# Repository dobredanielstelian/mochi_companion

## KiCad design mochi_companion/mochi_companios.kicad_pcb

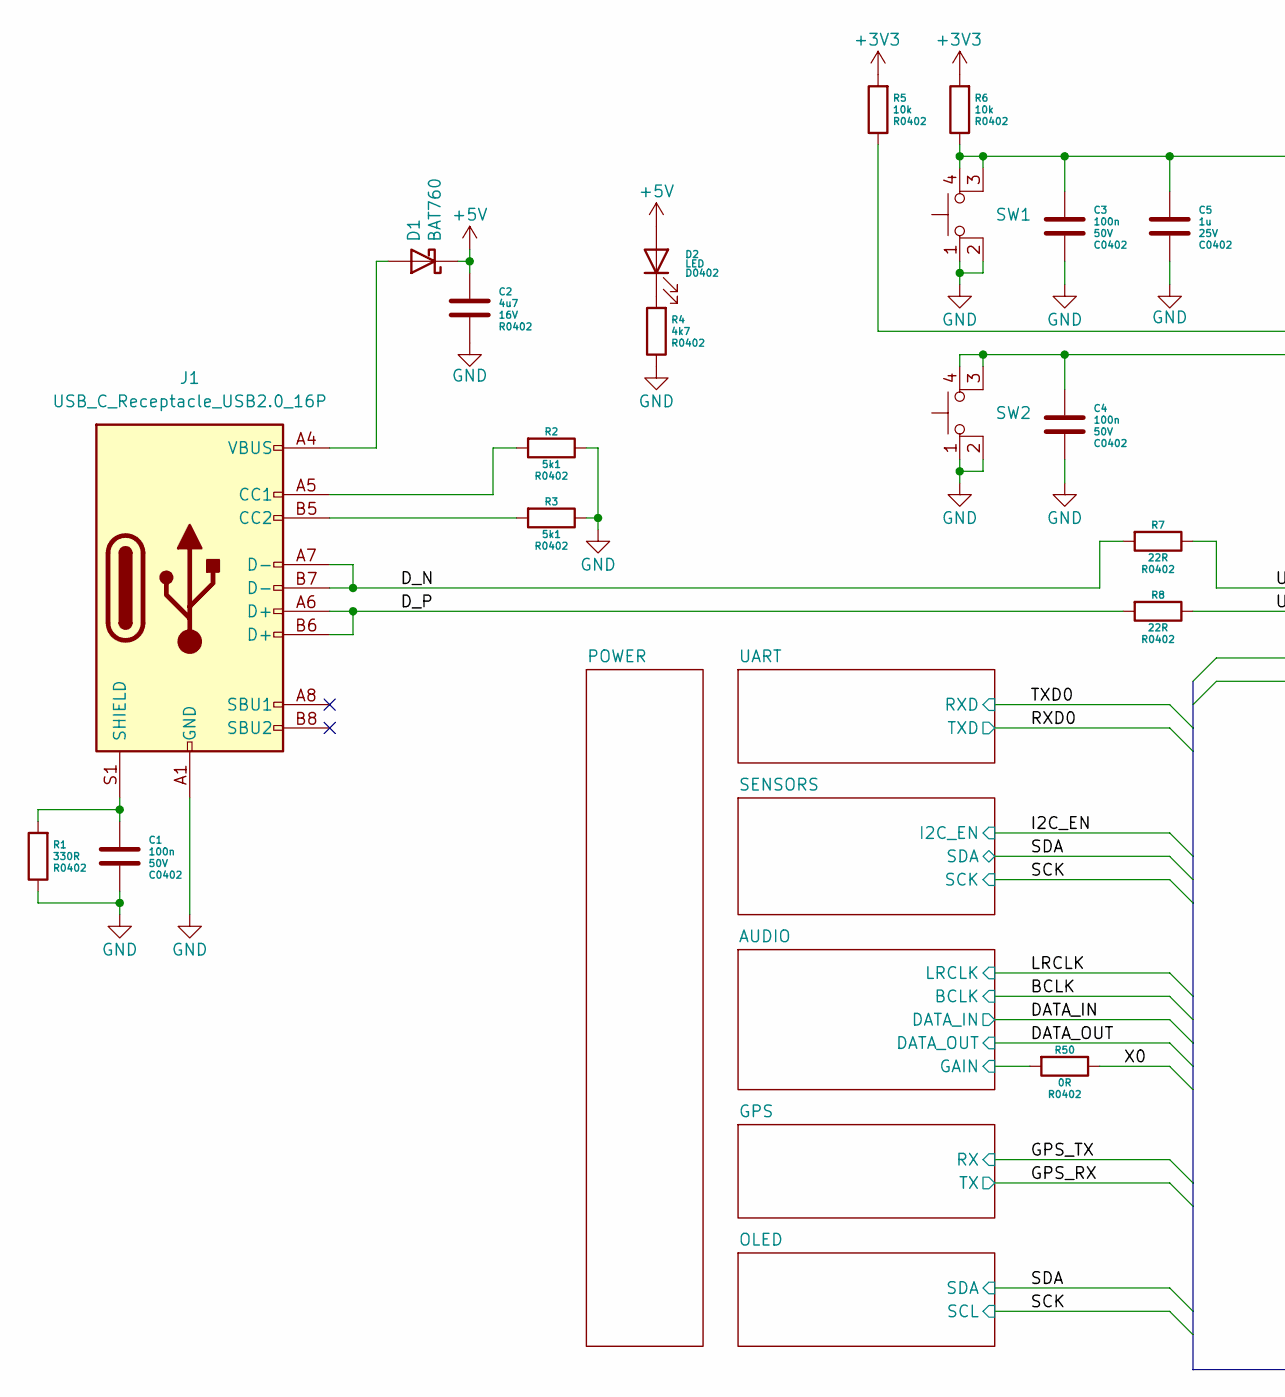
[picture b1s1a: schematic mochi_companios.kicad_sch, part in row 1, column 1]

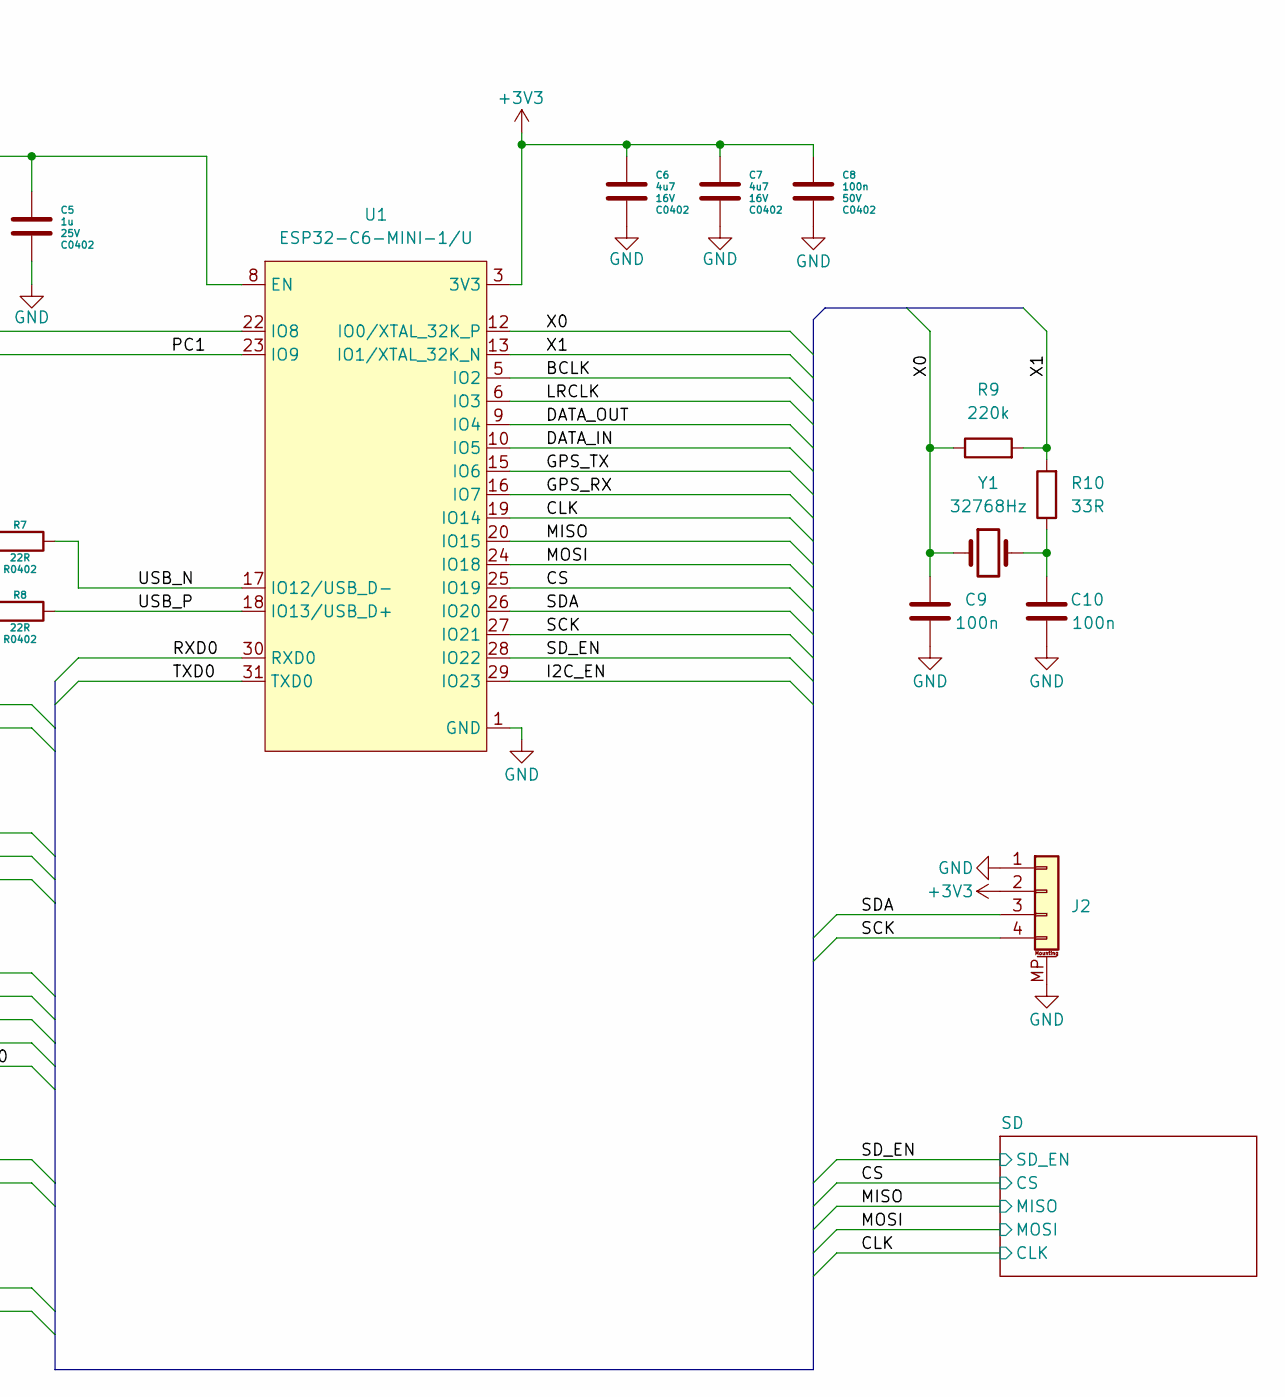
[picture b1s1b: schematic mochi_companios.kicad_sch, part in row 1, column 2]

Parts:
C1, C3, C4, C8, C9, C10: 100n; C_0402_1005Metric
C2, C6, C7: 4u7; C_0402_1005Metric
C5: 1u; C_0402_1005Metric
D1: BAT760; D_SOD-323
D2: LED; D_0402_1005Metric
J1: USB_C_Receptacle_USB2.0_16P; USB_C_Receptacle_Palconn_UTC16-G
J2: Conn_01x04_MountingPin; JST_SH_SM04B-SRSS-TB_1x04-1MP_P1.00mm_Horizontal
R1: 330R; R_0402_1005Metric
R2, R3: 5k1; R_0402_1005Metric
R4: 4k7; R_0402_1005Metric
R5, R6: 10k; R_0402_1005Metric
R7, R8: 22R; R_0402_1005Metric
R9: 220k; R_0402_1005Metric
R10: 33R; R_0402_1005Metric
R50: 0R; R_0402_1005Metric
SW1, SW2: 1TS026A-2300-0553-CT
U1: ESP32-C6-MINI-1/U; ESP32-C6-MINI-1
Y1: 32768Hz; Crystal_SMD_2012-2Pin_2.0x1.2mm

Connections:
+3V3: C6.1, C7.1, C8.1, J2.2, R5.2, R6.2, U1.3 (3V3); also elsewhere on the board
+5V: C2.1, D1.1 (K), D2.2 (A); also elsewhere on the board
/AUDIO/GAIN: R50.2; also elsewhere on the board
/BCLK: U1.5 (IO2); also elsewhere on the board
/CLK: U1.19 (IO14); also elsewhere on the board
/CS: U1.25 (IO19); also elsewhere on the board
/DATA_IN: U1.10 (IO5); also elsewhere on the board
/DATA_OUT: U1.9 (IO4); also elsewhere on the board
/D_N: J1.A7 (D-), J1.B7 (D-), R7.2
/D_P: J1.A6 (D+), J1.B6 (D+), R8.2
/GPS_RX: U1.16 (IO7); also elsewhere on the board
/GPS_TX: U1.15 (IO6); also elsewhere on the board
/I2C_EN: U1.29 (IO23); also elsewhere on the board
/LRCLK: U1.6 (IO3); also elsewhere on the board
/MISO: U1.20 (IO15); also elsewhere on the board
/MOSI: U1.24 (IO18); also elsewhere on the board
/PC1: C4.1, SW2.3 (K), SW2.4 (A), U1.23 (IO9)
/RXD0: U1.30 (RXD0); also elsewhere on the board
/SCK: J2.4, U1.27 (IO21); also elsewhere on the board
/SDA: J2.3, U1.26 (IO20); also elsewhere on the board
/SD_EN: U1.28 (IO22); also elsewhere on the board
/TXD0: U1.31 (TXD0); also elsewhere on the board
/USB_N: R7.1, U1.17 (IO12/USB_D-)
/USB_P: R8.1, U1.18 (IO13/USB_D+)
/X0: C9.1, R9.1, R50.1, U1.12 (IO0/XTAL_32K_P), Y1.1
/X1: R9.2, R10.2, U1.13 (IO1/XTAL_32K_N)
GND: C1.2, C2.2, C3.2, C4.2, C5.2, C6.2, C7.2, C8.2, C9.2, C10.2, J1.A1 (GND), J1.A12 (GND), J1.B1 (GND), J1.B12 (GND), J2.1, J2.MP (MountPin), R1.1, R2.1, R3.1, R4.1, SW1.1, SW1.2, SW2.1, SW2.2, U1.1 (GND), U1.2 (GND), U1.11 (GND), U1.14 (GND), U1.36 (GND), U1.37 (GND), U1.38 (GND), U1.39 (GND), U1.40 (GND), U1.41 (GND), U1.42 (GND), U1.43 (GND), U1.44 (GND), U1.45 (GND), U1.46 (GND), U1.47 (GND), U1.48 (GND), U1.49 (GND), U1.50 (GND), U1.51 (GND), U1.52 (GND), U1.53 (GND); also elsewhere on the board
unnamed: C10.1, R10.1, Y1.2
unnamed: D1.2 (A), J1.A4 (VBUS), J1.A9 (VBUS), J1.B4 (VBUS), J1.B9 (VBUS)
unnamed: D2.1 (K), R4.2
unnamed: J1.A5 (CC1), R2.2
unnamed: J1.B5 (CC2), R3.2
unnamed: C1.1, J1.S1 (SHIELD), R1.2
unnamed: C3.1, C5.1, R6.1, SW1.3 (K), SW1.4 (A), U1.8 (EN)
unnamed: R5.1, U1.22 (IO8)
unnamed: U1.4 (NC), U1.7 (NC), U1.21 (NC), U1.32 (NC), U1.33 (NC), U1.34 (NC), U1.35 (NC)

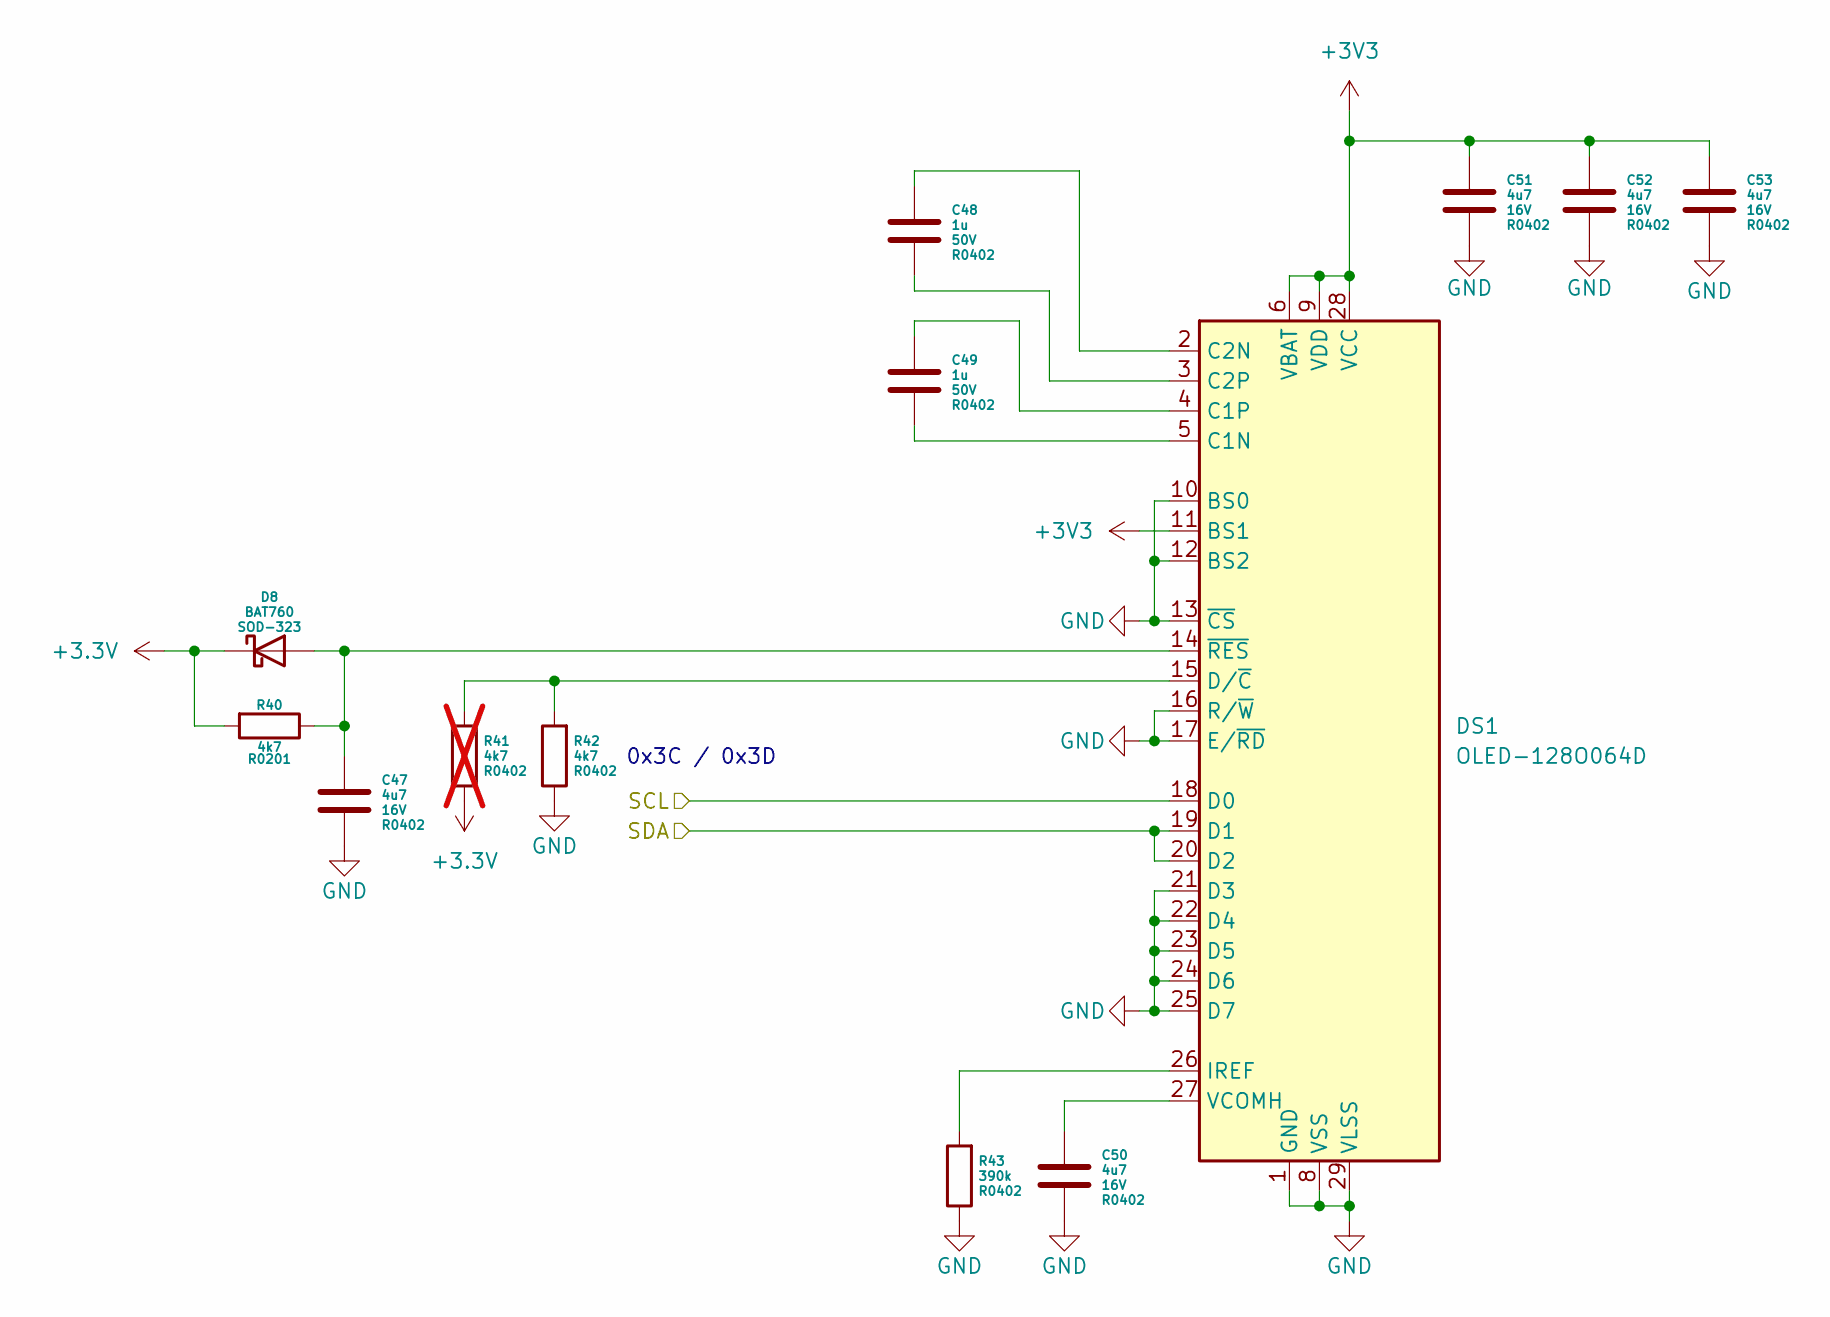
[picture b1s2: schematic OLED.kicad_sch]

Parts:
C47, C50, C51, C52, C53: 4u7; C_0402_1005Metric
C48, C49: 1u; C_0402_1005Metric
D8: BAT760; D_SOD-323
DS1: OLED-128O064D
R40: 4k7; R_0201_0603Metric
R41: 4k7; R_0402_1005Metric; not fitted
R42: 4k7; R_0402_1005Metric
R43: 390k; R_0402_1005Metric

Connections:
+3.3V: D8.1 (K), R40.2, R41.1; also elsewhere on the board
+3V3: C51.1, C52.1, C53.1, DS1.6 (VBAT), DS1.9 (VDD), DS1.11 (BS1), DS1.28 (VCC); also elsewhere on the board
/SCK: DS1.18 (D0); also elsewhere on the board
/SDA: DS1.19 (D1), DS1.20 (D2); also elsewhere on the board
GND: C47.2, C50.2, C51.2, C52.2, C53.2, DS1.1 (GND), DS1.8 (VSS), DS1.10 (BS0), DS1.12 (BS2), DS1.13 (~CS), DS1.16 (R/~W), DS1.17 (E/~RD), DS1.21 (D3), DS1.22 (D4), DS1.23 (D5), DS1.24 (D6), DS1.25 (D7), DS1.29 (VLSS), DS1.30 (GND), R42.1, R43.1; also elsewhere on the board
unnamed: C47.1, D8.2 (A), DS1.14 (~RES), R40.1
unnamed: C49.2, DS1.5 (C1N)
unnamed: C49.1, DS1.4 (C1P)
unnamed: C48.1, DS1.2 (C2N)
unnamed: C48.2, DS1.3 (C2P)
unnamed: DS1.15 (D/~C), R41.2, R42.2
unnamed: DS1.26 (IREF), R43.2
unnamed: C50.1, DS1.27 (VCOMH)

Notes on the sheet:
0x3C / 0x3D

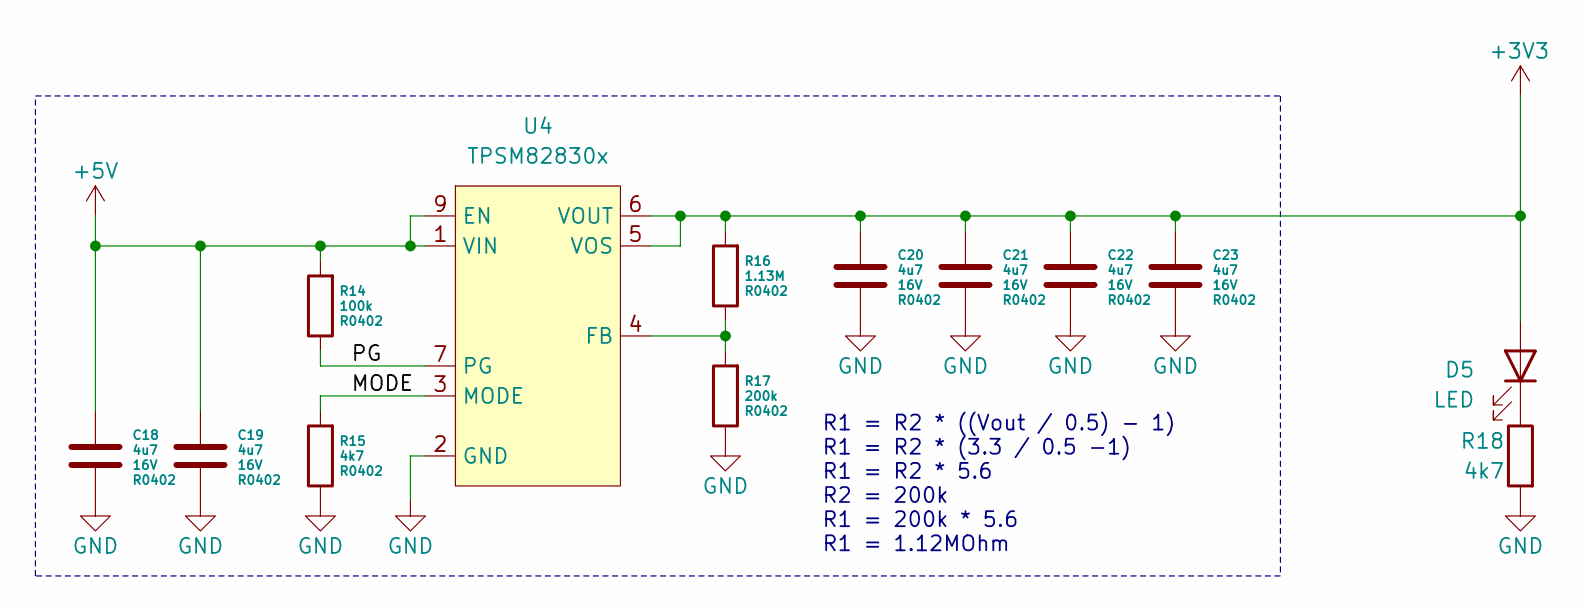
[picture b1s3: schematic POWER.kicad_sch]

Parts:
C18, C19, C20, C21, C22, C23: 4u7; C_0402_1005Metric
D5: LED; D_0402_1005Metric
R14: 100k; R_0402_1005Metric
R15, R18: 4k7; R_0402_1005Metric
R16: 1.13M; R_0402_1005Metric
R17: 200k; R_0402_1005Metric
U4: TPSM82830x; TPSM82830x_QFN-FCMOD

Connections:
+3V3: C20.1, C21.1, C22.1, C23.1, D5.2 (A), R16.2, U4.5 (VOS), U4.6 (VOUT); also elsewhere on the board
+5V: C18.1, C19.1, R14.2, U4.1 (VIN), U4.9 (EN); also elsewhere on the board
/POWER/MODE: R15.2, U4.3 (MODE)
/POWER/PG: R14.1, U4.7 (PG)
GND: C18.2, C19.2, C20.2, C21.2, C22.2, C23.2, R15.1, R17.1, R18.2, U4.2 (GND); also elsewhere on the board
unnamed: D5.1 (K), R18.1
unnamed: R16.1, R17.2, U4.4 (FB)

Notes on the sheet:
R1 = R2 * ((Vout / 0.5) - 1) R1 = R2 * (3.3 / 0.5 -1) R1 = R2 * 5.6 R2 = 200k R1 = 200k * 5.6 R1 = 1.12MOhm

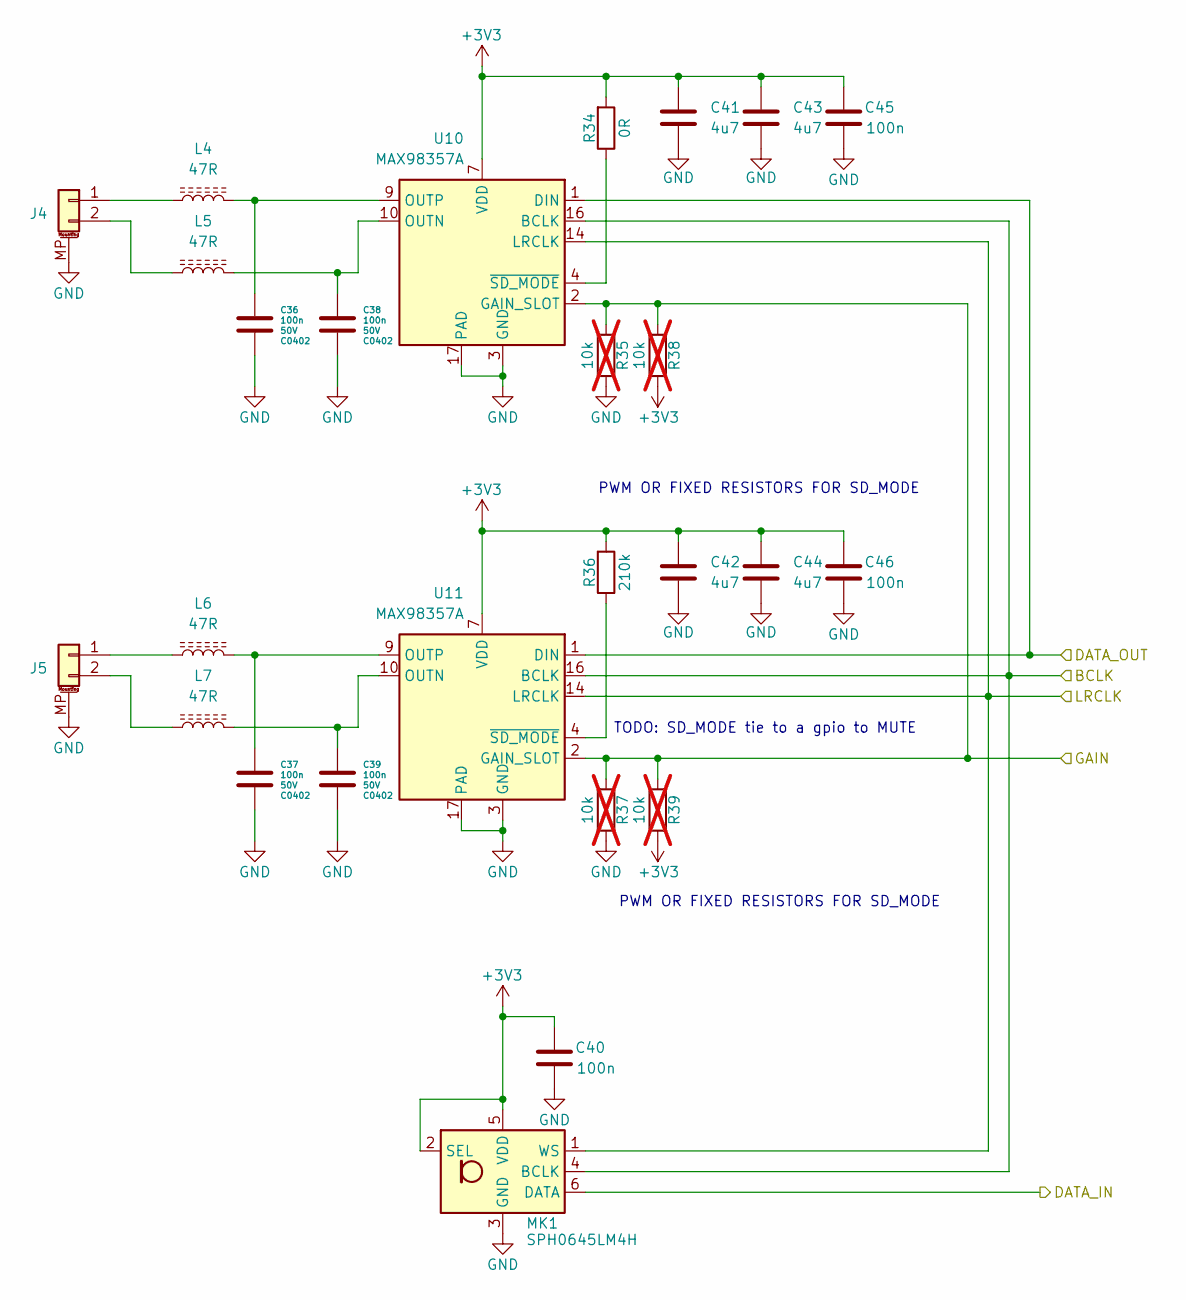
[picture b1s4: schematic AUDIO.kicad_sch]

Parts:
C36, C37, C38, C39, C40, C45, C46: 100n; C_0402_1005Metric
C41, C42, C43, C44: 4u7; C_0402_1005Metric
J4, J5: Conn_01x02_MountingPin; JST_SHL_SM02B-SHLS-TF_1x02-1MP_P1.00mm_Horizontal
L4, L5, L6, L7: 47R; L_0402_1005Metric
MK1: SPH0645LM4H; Knowles_SPH0645LM4H-6_3.5x2.65mm
R34: 0R; R_0402_1005Metric
R35, R37, R38, R39: 10k; R_0402_1005Metric; not fitted
R36: 210k; R_0402_1005Metric
U10, U11: MAX98357A; TQFN-16-1EP_3x3mm_P0.5mm_EP1.23x1.23mm

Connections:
+3V3: C40.1, C41.1, C42.1, C43.1, C44.1, C45.1, C46.1, MK1.2 (SEL), MK1.5 (VDD), R34.2, R36.2, R38.2, R39.2, U10.7 (VDD), U10.8 (VDD), U11.7 (VDD), U11.8 (VDD); also elsewhere on the board
/AUDIO/GAIN: R35.1, R37.1, R38.1, R39.1, U10.2 (GAIN_SLOT), U11.2 (GAIN_SLOT); also elsewhere on the board
/BCLK: MK1.4 (BCLK), U10.16 (BCLK), U11.16 (BCLK); also elsewhere on the board
/DATA_IN: MK1.6 (DATA); also elsewhere on the board
/DATA_OUT: U10.1 (DIN), U11.1 (DIN); also elsewhere on the board
/LRCLK: MK1.1 (WS), U10.14 (LRCLK), U11.14 (LRCLK); also elsewhere on the board
GND: C36.2, C37.2, C38.2, C39.2, C40.2, C41.2, C42.2, C43.2, C44.2, C45.2, C46.2, J4.MP (MountPin), J5.MP (MountPin), MK1.3 (GND), R35.2, R37.2, U10.3 (GND), U10.11 (GND), U10.15 (GND), U10.17 (PAD), U11.3 (GND), U11.11 (GND), U11.15 (GND), U11.17 (PAD); also elsewhere on the board
unnamed: J4.1, L4.1
unnamed: J4.2, L5.1
unnamed: J5.1, L6.1
unnamed: J5.2, L7.1
unnamed: C38.1, L5.2, U10.10 (OUTN)
unnamed: C36.1, L4.2, U10.9 (OUTP)
unnamed: R34.1, U10.4 (~SD_MODE)
unnamed: C39.1, L7.2, U11.10 (OUTN)
unnamed: C37.1, L6.2, U11.9 (OUTP)
unnamed: R36.1, U11.4 (~SD_MODE)

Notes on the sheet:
PWM OR FIXED RESISTORS FOR SD_MODE
TODO: SD_MODE tie to a gpio to MUTE

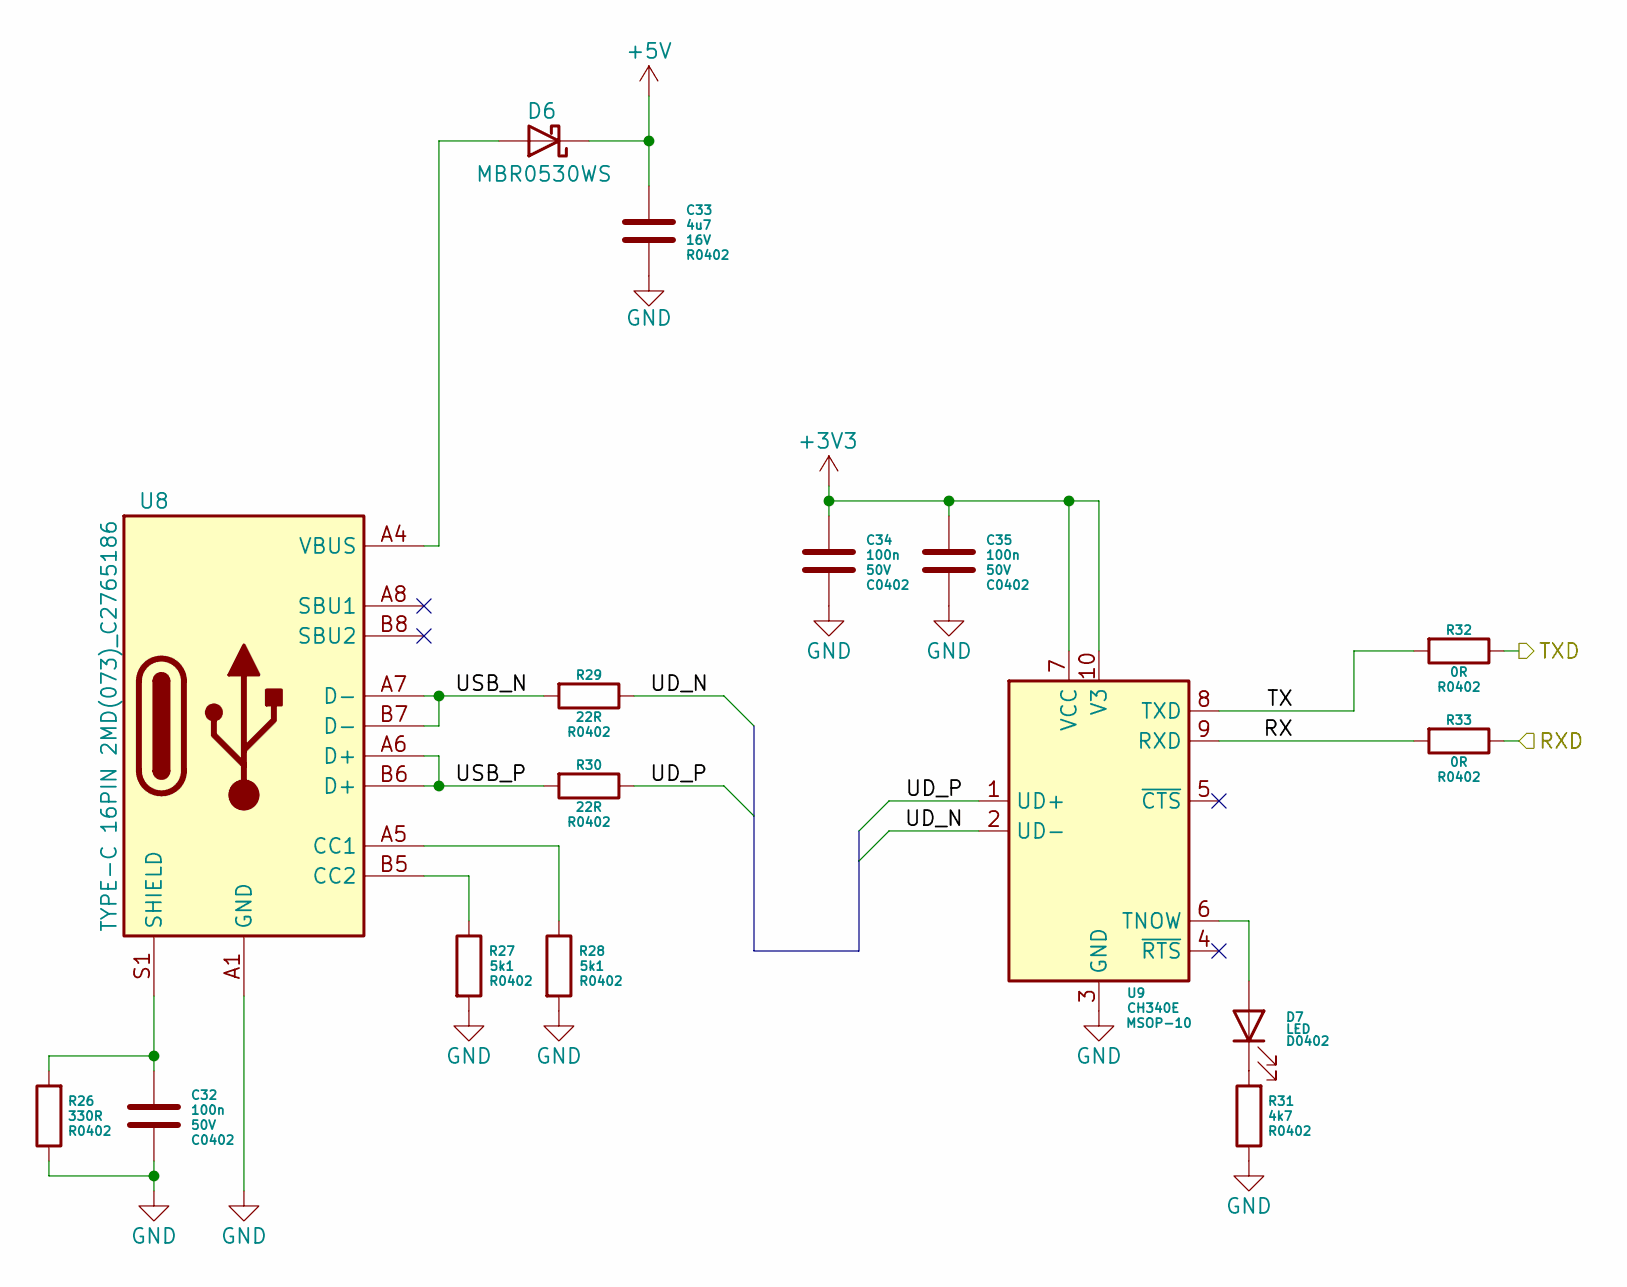
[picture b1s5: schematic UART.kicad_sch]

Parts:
C32, C34, C35: 100n; C_0402_1005Metric
C33: 4u7; C_0402_1005Metric
D6: MBR0530WS; D_SOD-323
D7: LED; D_0402_1005Metric
R26: 330R; R_0402_1005Metric
R27, R28: 5k1; R_0402_1005Metric
R29, R30: 22R; R_0402_1005Metric
R31: 4k7; R_0402_1005Metric
R32, R33: 0R; R_0402_1005Metric
U8: TYPE-C 16PIN 2MD(073)_C2765186; USB_C_Receptacle_Palconn_UTC16-G
U9: CH340E; MSOP-10_3x3mm_P0.5mm

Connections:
+3V3: C34.1, C35.1, U9.7 (VCC), U9.10 (V3); also elsewhere on the board
+5V: C33.1, D6.1 (K); also elsewhere on the board
/RXD0: R32.1; also elsewhere on the board
/TXD0: R33.1; also elsewhere on the board
/UART/RX: R33.2, U9.9 (RXD)
/UART/TX: R32.2, U9.8 (TXD)
/UART/UD_N: R29.1, U9.2 (UD-)
/UART/UD_P: R30.1, U9.1 (UD+)
/UART/USB_N: R29.2, U8.A7 (D-), U8.B7 (D-)
/UART/USB_P: R30.2, U8.A6 (D+), U8.B6 (D+)
GND: C32.2, C33.2, C34.2, C35.2, R26.1, R27.2, R28.2, R31.1, U8.A1 (GND), U8.A12 (GND), U8.B1 (GND), U8.B12 (GND), U9.3 (GND); also elsewhere on the board
unnamed: D6.2 (A), U8.A4 (VBUS), U8.A9 (VBUS), U8.B4 (VBUS), U8.B9 (VBUS)
unnamed: D7.2 (A), U9.6 (TNOW)
unnamed: D7.1 (K), R31.2
unnamed: R28.1, U8.A5 (CC1)
unnamed: R27.1, U8.B5 (CC2)
unnamed: C32.1, R26.2, U8.S1 (SHIELD)

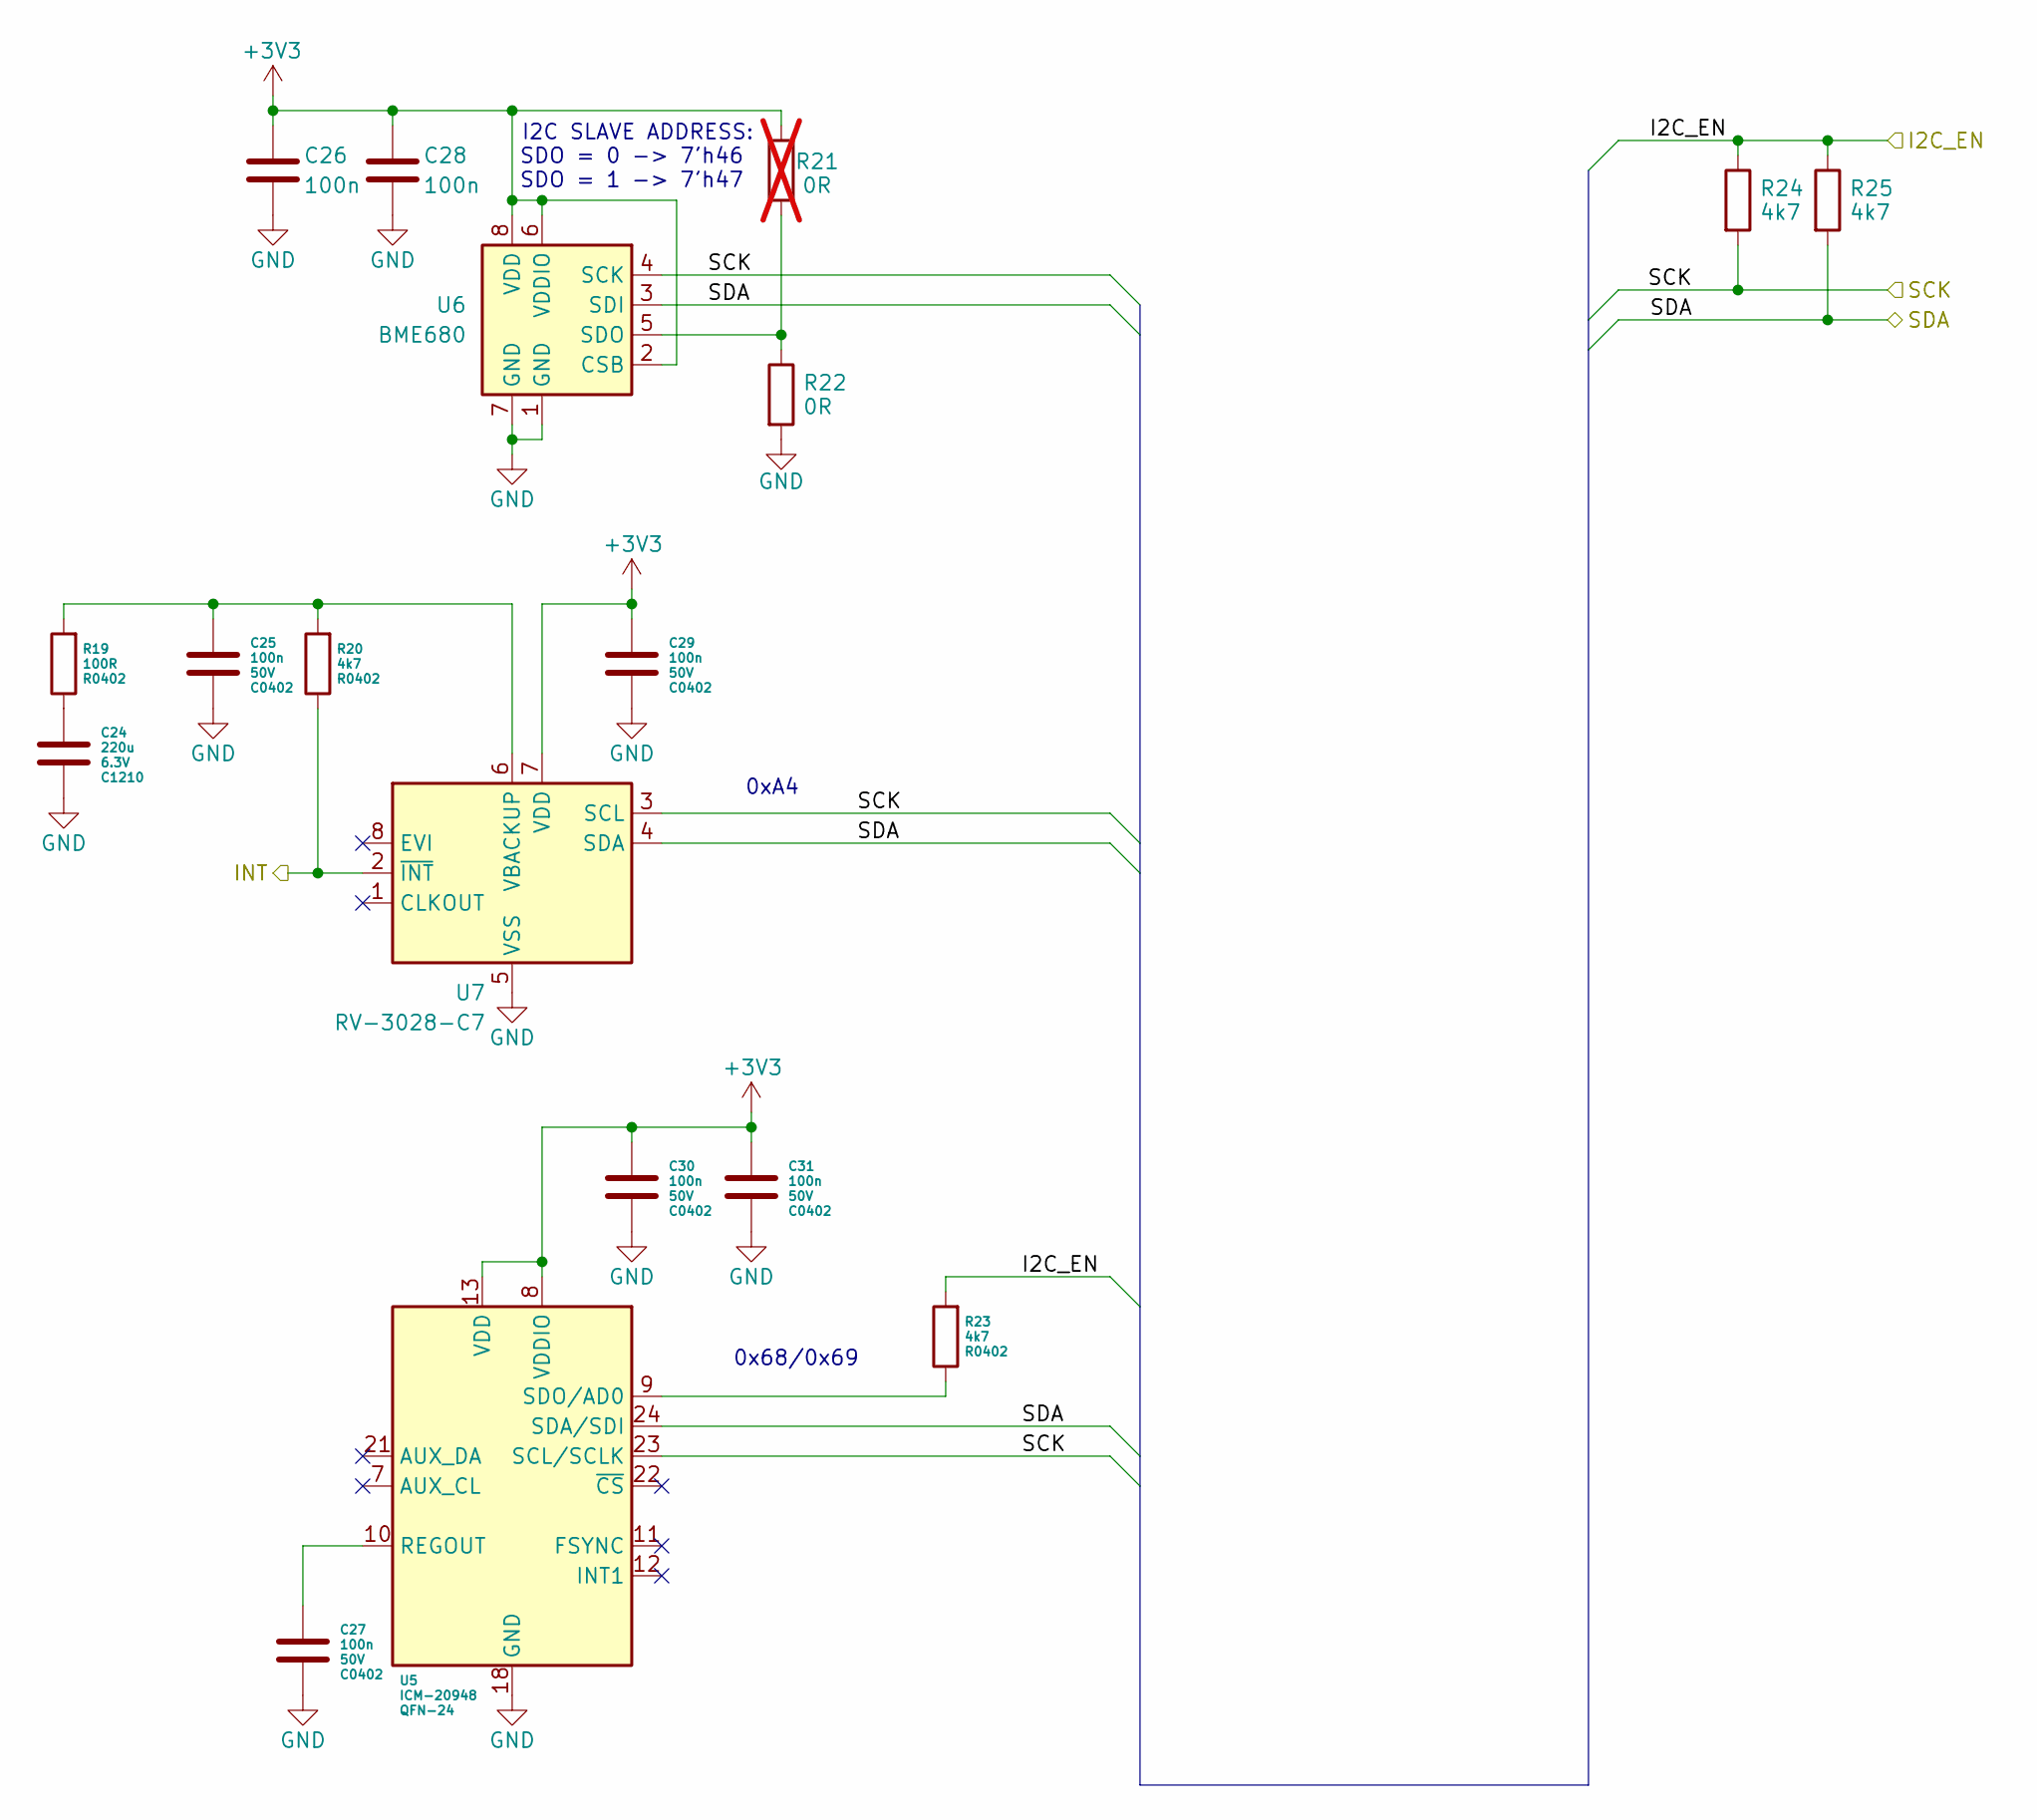
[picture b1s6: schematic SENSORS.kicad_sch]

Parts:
C24: 220u; C_1210_3225Metric
C25, C26, C27, C28, C29, C30, C31: 100n; C_0402_1005Metric
R19: 100R; R_0402_1005Metric
R20, R23, R24, R25: 4k7; R_0402_1005Metric
R21: 0R; R_0402_1005Metric; not fitted
R22: 0R; R_0402_1005Metric
U5: ICM-20948; InvenSense_QFN-24_3x3mm_P0.4mm
U6: BME680; Bosch_LGA-8_3x3mm_P0.8mm_ClockwisePinNumbering
U7: RV-3028-C7

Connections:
+3V3: C26.1, C28.1, C29.1, C30.1, C31.1, R21.2, U5.8 (VDDIO), U5.13 (VDD), U6.2 (CSB), U6.6 (VDDIO), U6.8 (VDD), U7.7 (VDD); also elsewhere on the board
/I2C_EN: R23.2, R24.1, R25.1; also elsewhere on the board
/SCK: R24.2, U5.23 (SCL/SCLK), U6.4 (SCK), U7.3 (SCL); also elsewhere on the board
/SDA: R25.2, U5.24 (SDA/SDI), U6.3 (SDI), U7.4 (SDA); also elsewhere on the board
/SENSORS/INT: R20.1, U7.2 (~INT)
GND: C24.2, C25.2, C26.2, C27.2, C28.2, C29.2, C30.2, C31.2, R22.2, U5.18 (GND), U5.20 (GND), U6.1 (GND), U6.7 (GND), U7.5 (VSS); also elsewhere on the board
unnamed: C24.1, R19.1
unnamed: C27.1, U5.10 (REGOUT)
unnamed: R23.1, U5.9 (SDO/AD0)
unnamed: R21.1, R22.1, U6.5 (SDO)
unnamed: C25.1, R19.2, R20.2, U7.6 (VBACKUP)

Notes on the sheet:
0xA4
SDO = 0 -> 7'h46 SDO = 1 -> 7'h47
0x68/0x69
I2C SLAVE ADDRESS:

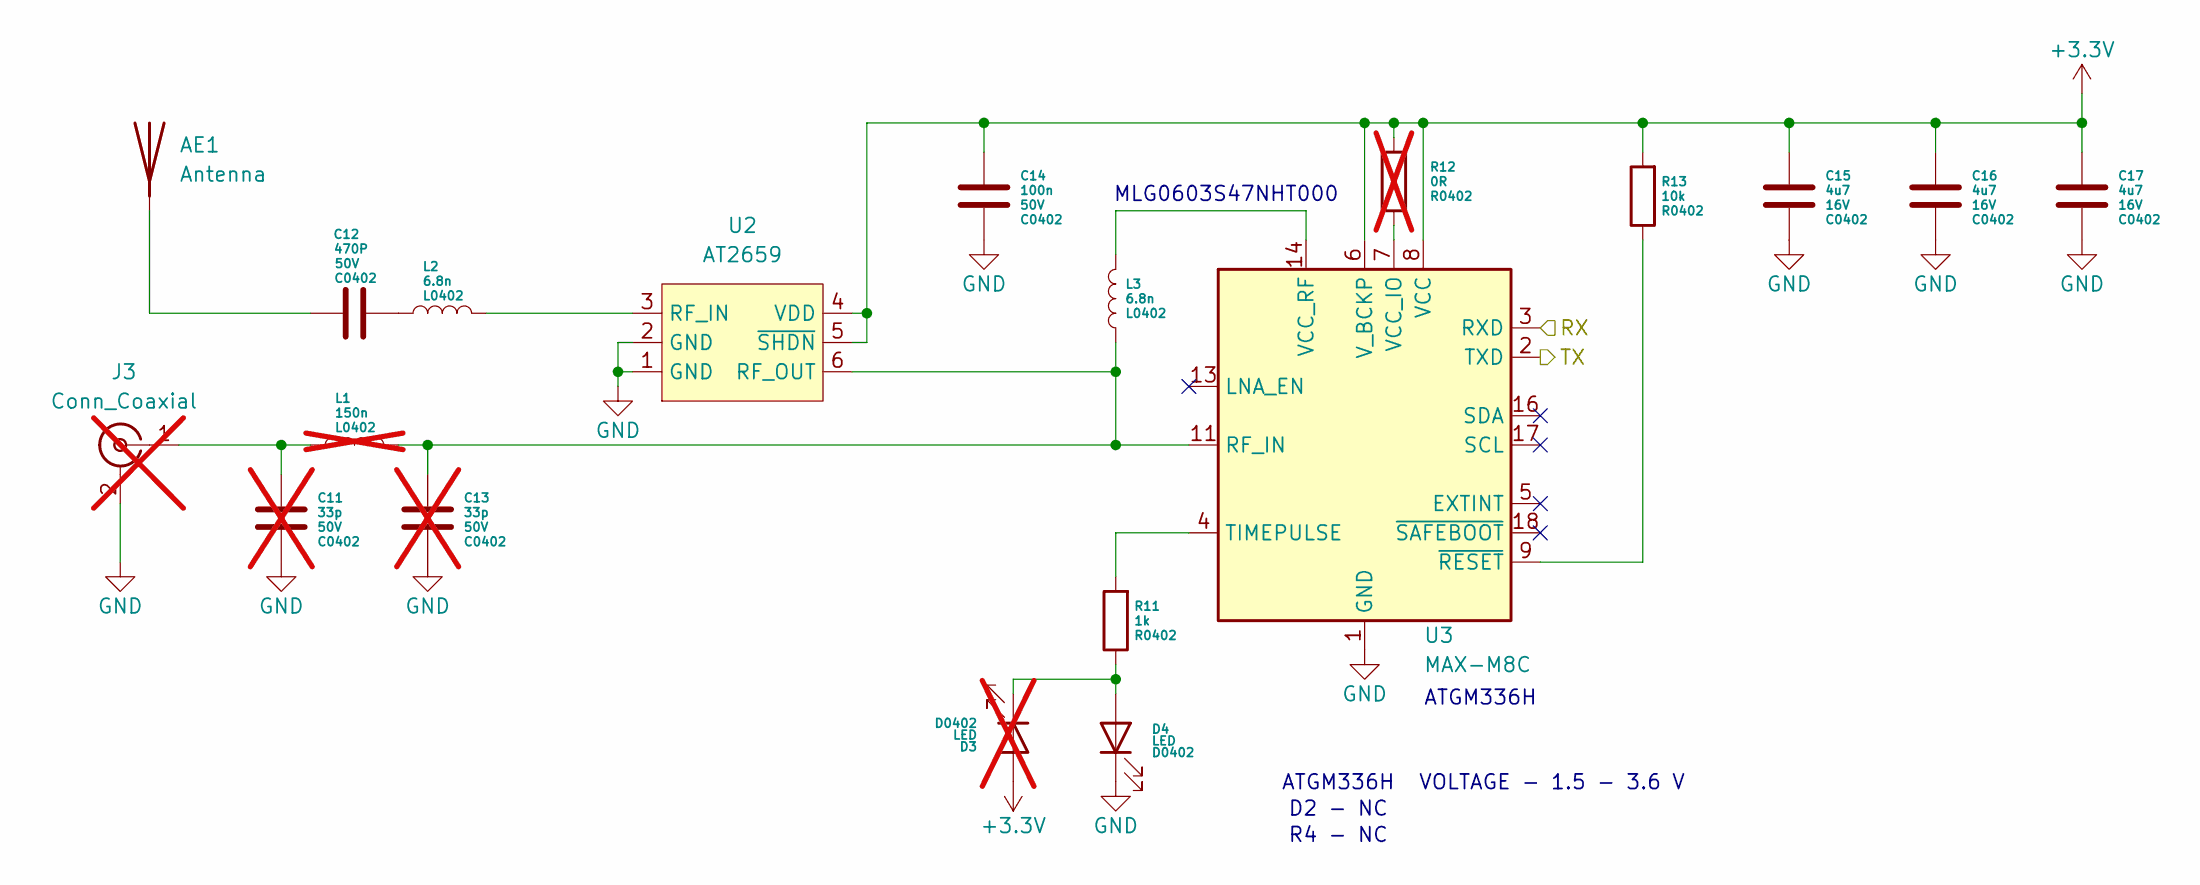
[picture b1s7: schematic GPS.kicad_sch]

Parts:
AE1: Antenna; TestPoint_THTPad_1.0x1.0mm_Drill0.5mm
C11, C13: 33p; C_0402_1005Metric; not fitted
C12: 470P; C_0402_1005Metric
C14: 100n; C_0402_1005Metric
C15, C16, C17: 4u7; C_0402_1005Metric
D3: LED; D_0402_1005Metric; not fitted
D4: LED; D_0402_1005Metric
J3: Conn_Coaxial; U.FL_Molex_MCRF_73412-0110_Vertical; not fitted
L1: 150n; L_0402_1005Metric; not fitted
L2, L3: 6.8n; L_0402_1005Metric
R11: 1k; R_0402_1005Metric
R12: 0R; R_0402_1005Metric; not fitted
R13: 10k; R_0402_1005Metric
U2: AT2659; DFN-6_1x1.5_Pitch0.5mm_AT2659
U3: MAX-M8C; ublox_MAX

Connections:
+3.3V: C14.1, C15.1, C16.1, C17.1, D3.2 (A), R12.2, R13.2, U2.4 (VDD), U2.5 (~SHDN), U3.6 (V_BCKP), U3.8 (VCC); also elsewhere on the board
/GPS_RX: U3.2 (TXD); also elsewhere on the board
/GPS_TX: U3.3 (RXD); also elsewhere on the board
GND: C11.2, C13.2, C14.2, C15.2, C16.2, C17.2, D4.1 (K), J3.2 (Ext), U2.1 (GND), U2.2 (GND), U3.1 (GND), U3.10 (GND), U3.12 (GND); also elsewhere on the board
unnamed: AE1.1 (A), C12.1
unnamed: C12.2, L2.1
unnamed: D3.1 (K), D4.2 (A), R11.1
unnamed: C11.1, J3.1 (In), L1.1
unnamed: L2.2, U2.3 (RF_IN)
unnamed: C13.1, L1.2, L3.1, U2.6 (RF_OUT), U3.11 (RF_IN)
unnamed: R11.2, U3.4 (TIMEPULSE)
unnamed: R12.1, U3.7 (VCC_IO)
unnamed: L3.2, U3.14 (VCC_RF)
unnamed: R13.1, U3.9 (~RESET)

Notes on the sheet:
D2 - NC
VOLTAGE - 1.5 - 3.6 V
ATGM336H
R4 - NC
MLG0603S47NHT000
